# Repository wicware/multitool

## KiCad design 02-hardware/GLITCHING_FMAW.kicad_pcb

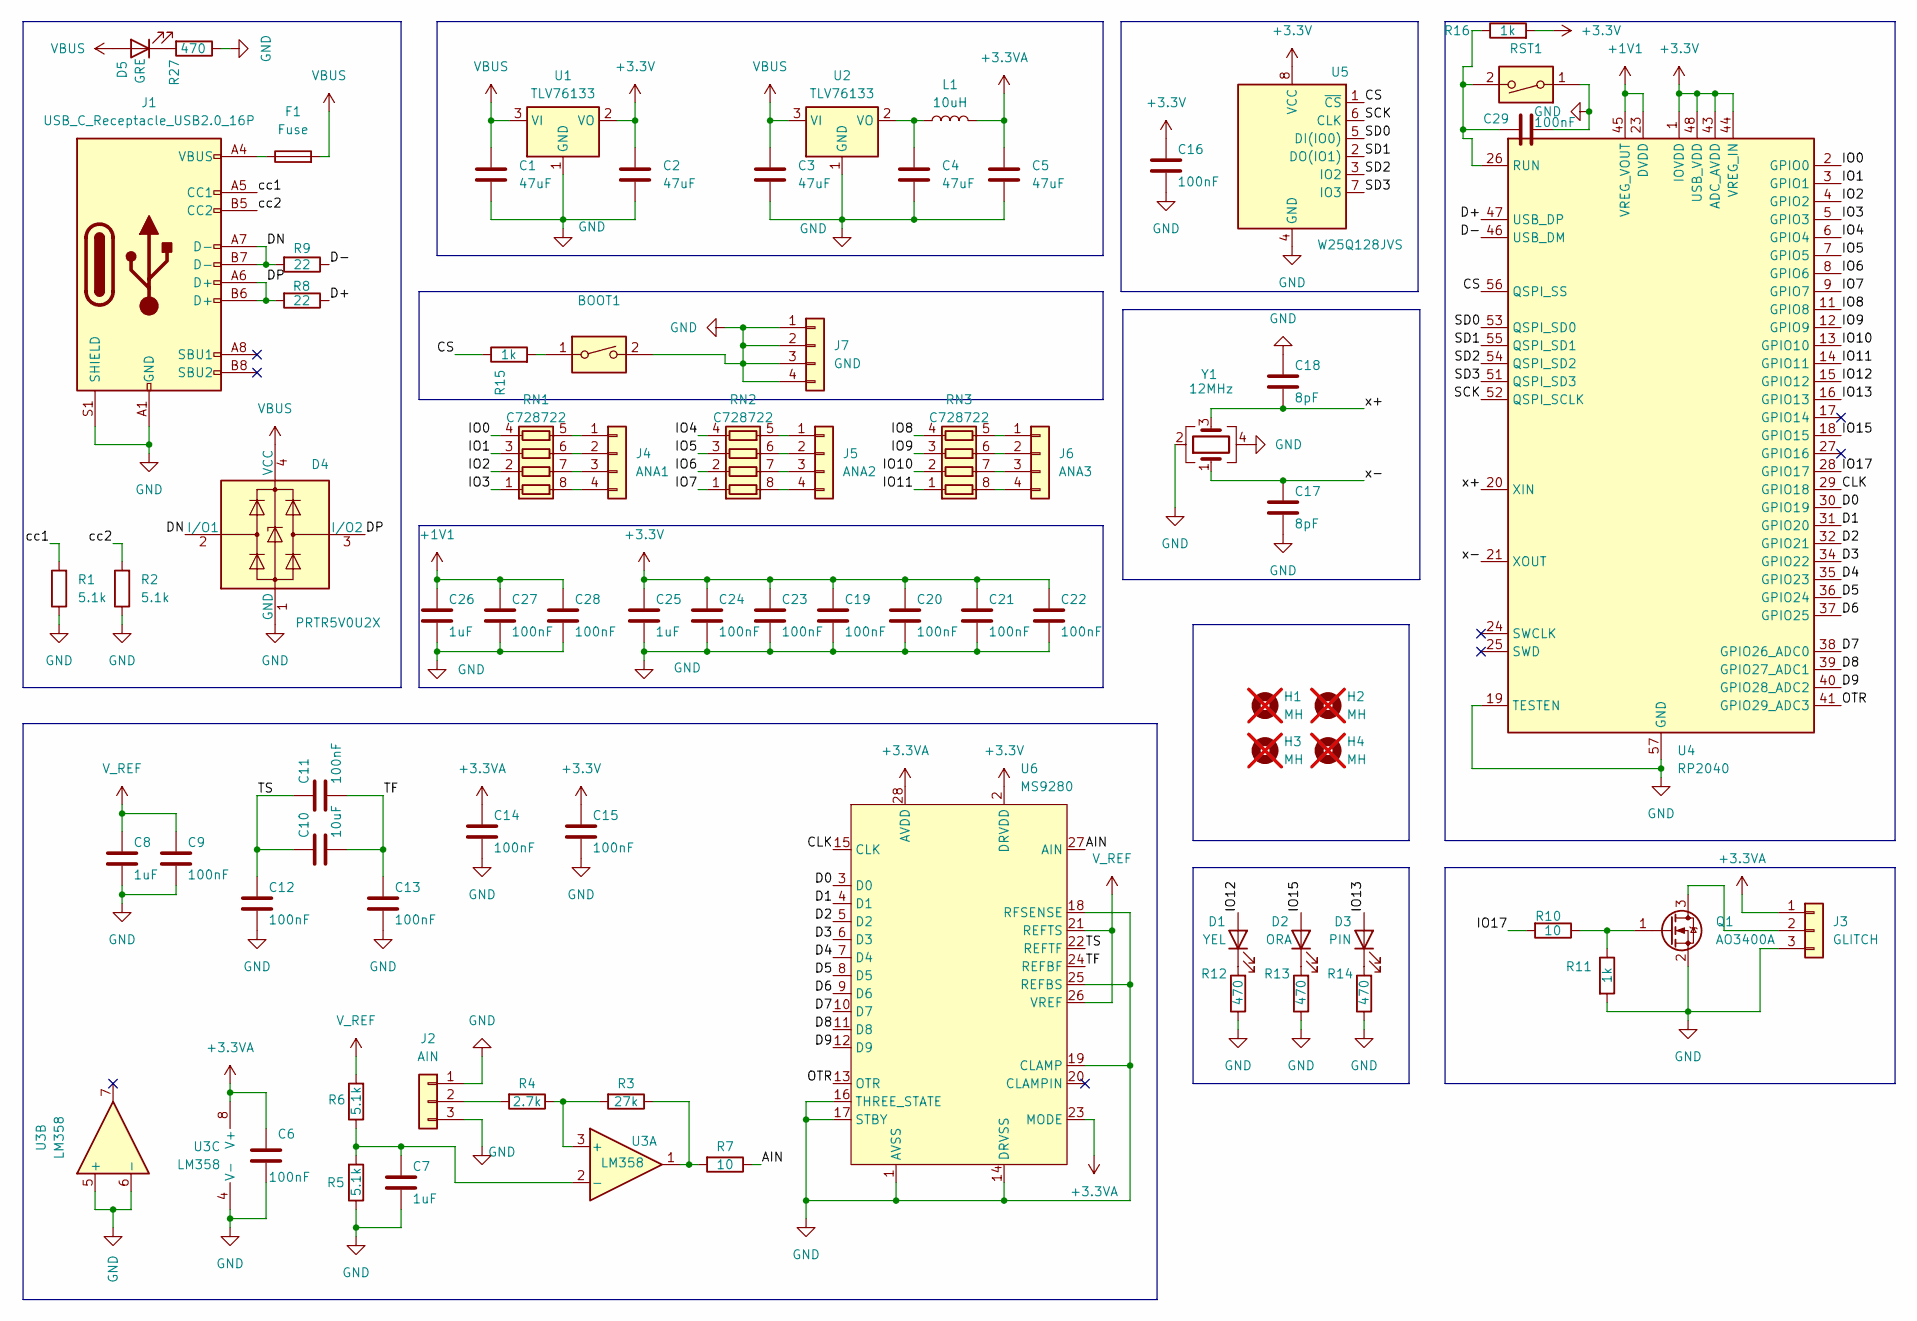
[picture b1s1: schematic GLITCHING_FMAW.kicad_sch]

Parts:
BOOT1: SW_DIP_x01; SW_SPST_CK_RS282G05A3
C1, C2, C3, C4, C5: 47uF; C_1206_3216Metric
C6, C9, C11, C12, C13, C14, C15, C16, C19, C20, C21, C22, C23, C24, C27, C28, C29: 100nF; C_0603_1608Metric
C7, C8, C25, C26: 1uF; C_0603_1608Metric
C10: 10uF; C_0603_1608Metric
C17, C18: 8pF; C_0603_1608Metric
D1: YEL; LED_0603_1608Metric
D2: ORA; LED_0603_1608Metric
D3: PIN; LED_0603_1608Metric
D4: PRTR5V0U2X; SOT-143; LCSC C5180302
D5: GRE; LED_0603_1608Metric
F1: Fuse; Fuse_1812_4532Metric; LCSC C142689
H1, H2, H3, H4: MH; MountingHole_2.2mm_M2_DIN965_Pad; not fitted
J1: USB_C_Receptacle_USB2.0_16P; USB_C_Receptacle_GCT_USB4105-xx-A_16P_TopMnt_Horizontal
J2: AIN; PinHeader_1x03_P2.54mm_Vertical
J3: GLITCH; PinHeader_1x03_P2.54mm_Vertical
J4: ANA1; PinHeader_1x04_P2.54mm_Vertical
J5: ANA2; PinHeader_1x04_P2.54mm_Vertical
J6: ANA3; PinHeader_1x04_P2.54mm_Vertical
J7: GND; PinHeader_1x04_P2.54mm_Vertical
L1: 10uH; L_Bourns_SRP7028A_7.3x6.6mm; LCSC C22463829
Q1: AO3400A; SOT-23; LCSC C20917
R1, R2, R5, R6: 5.1k; R_0603_1608Metric
R3: 27k; R_0603_1608Metric
R4: 2.7k; R_0603_1608Metric
R7, R10: 10; R_0603_1608Metric
R8, R9: 22; R_0603_1608Metric
R11, R15, R16: 1k; R_0603_1608Metric
R12, R13, R14, R27: 470; R_0603_1608Metric
RN1, RN2, RN3: C728722; R_Array_Concave_4x0402; LCSC C728722
RST1: SW_DIP_x01; SW_SPST_CK_RS282G05A3
U1, U2: TLV76133; SOT-223-3_TabPin2; LCSC C7527500
U3: LM358; SO-8_3.9x4.9mm_P1.27mm; LCSC C693063
U4: RP2040; QFN-56-1EP_7x7mm_P0.4mm_EP3.2x3.2mm
U5: W25Q128JVS; SOIC-8_5.23x5.23mm_P1.27mm; LCSC C97521
U6: MS9280; SSOP-28_5.3x10.2mm_P0.65mm; LCSC C1509021
Y1: 12MHz; Crystal_SMD_Abracon_ABM10-4Pin_2.5x2.0mm; LCSC C1985454

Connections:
+1V1: C26.1, C27.1, C28.1, U4.23 (DVDD), U4.45 (VREG_VOUT), U4.50 (DVDD)
+3.3V: C2.1, C15.1, C16.1, C19.1, C20.1, C21.1, C22.1, C23.1, C24.1, C25.1, R16.2, U1.2 (VO), U4.1 (IOVDD), U4.10 (IOVDD), U4.22 (IOVDD), U4.33 (IOVDD), U4.42 (IOVDD), U4.43 (ADC_AVDD), U4.44 (VREG_IN), U4.48 (USB_VDD), U4.49 (IOVDD), U5.8 (VCC), U6.2 (DRVDD)
+3.3VA: C5.1, C6.1, C14.1, J3.1, L1.2, U3.8 (V+), U6.23 (MODE), U6.28 (AVDD)
/AIN: R7.1, U6.27 (AIN)
/CLK: U4.29 (GPIO18), U6.15 (CLK)
/CS: R15.1, U4.56 (QSPI_SS), U5.1 (~CS)
/D0: U4.30 (GPIO19), U6.3 (D0)
/D1: U4.31 (GPIO20), U6.4 (D1)
/D2: U4.32 (GPIO21), U6.5 (D2)
/D3: U4.34 (GPIO22), U6.6 (D3)
/D4: U4.35 (GPIO23), U6.7 (D4)
/D5: U4.36 (GPIO24), U6.8 (D5)
/D6: U4.37 (GPIO25), U6.9 (D6)
/D7: U4.38 (GPIO26_ADC0), U6.10 (D7)
/D8: U4.39 (GPIO27_ADC1), U6.11 (D8)
/D9: U4.40 (GPIO28_ADC2), U6.12 (D9)
/D+: R8.1, U4.47 (USB_DP)
/D-: R9.1, U4.46 (USB_DM)
/DN: D4.2 (I/O1), J1.A7 (D-), J1.B7 (D-), R9.2
/DP: D4.3 (I/O2), J1.A6 (D+), J1.B6 (D+), R8.2
/IO0: RN1.4 (R4.1), U4.2 (GPIO0)
/IO1: RN1.3 (R3.1), U4.3 (GPIO1)
/IO2: RN1.2 (R2.1), U4.4 (GPIO2)
/IO3: RN1.1 (R1.1), U4.5 (GPIO3)
/IO4: RN2.4 (R4.1), U4.6 (GPIO4)
/IO5: RN2.3 (R3.1), U4.7 (GPIO5)
/IO6: RN2.2 (R2.1), U4.8 (GPIO6)
/IO7: RN2.1 (R1.1), U4.9 (GPIO7)
/IO8: RN3.4 (R4.1), U4.11 (GPIO8)
/IO9: RN3.3 (R3.1), U4.12 (GPIO9)
/IO10: RN3.2 (R2.1), U4.13 (GPIO10)
/IO11: RN3.1 (R1.1), U4.14 (GPIO11)
/IO12: D1.2 (A), U4.15 (GPIO12)
/IO13: D3.2 (A), U4.16 (GPIO13)
/IO15: D2.2 (A), U4.18 (GPIO15)
/IO17: R10.2, U4.28 (GPIO17)
/OTR: U4.41 (GPIO29_ADC3), U6.13 (OTR)
/SCK: U4.52 (QSPI_SCLK), U5.6 (CLK)
/SD0: U4.53 (QSPI_SD0), U5.5 (DI(IO0))
/SD1: U4.55 (QSPI_SD1), U5.2 (DO(IO1))
/SD2: U4.54 (QSPI_SD2), U5.3 (IO2)
/SD3: U4.51 (QSPI_SD3), U5.7 (IO3)
/TF: C10.2, C11.2, C13.1, U6.24 (REFBF)
/TS: C10.1, C11.1, C12.1, U6.22 (REFTF)
/cc1: J1.A5 (CC1), R1.2
/cc2: J1.B5 (CC2), R2.2
/x+: C18.2, U4.20 (XIN), Y1.3
/x-: C17.1, U4.21 (XOUT), Y1.1
GND: BOOT1.2, C1.2, C2.2, C3.2, C4.2, C5.2, C6.2, C7.2, C8.2, C9.2, C12.2, C13.2, C14.2, C15.2, C16.2, C17.2, C18.1, C19.2, C20.2, C21.2, C22.2, C23.2, C24.2, C25.2, C26.2, C27.2, C28.2, C29.2, D4.1 (GND), J1.A1 (GND), J1.A12 (GND), J1.B1 (GND), J1.B12 (GND), J1.S1 (SHIELD), J2.1, J2.3, J3.3, J7.1, J7.2, J7.3, J7.4, Q1.2 (S), R1.1, R2.1, R5.1, R11.2, R12.1, R13.1, R14.1, R27.1, RST1.1, U1.1 (GND), U2.1 (GND), U3.4 (V-), U3.5 (+), U3.6 (-), U4.19 (TESTEN), U4.57 (GND), U5.4 (GND), U6.1 (AVSS), U6.14 (DRVSS), U6.16 (THREE_STATE), U6.17 (STBY), U6.18 (RFSENSE), U6.19 (CLAMP), U6.25 (REFBS), Y1.2, Y1.4
unnamed: BOOT1.1, R15.2
unnamed: D1.1 (K), R12.2
unnamed: D2.1 (K), R13.2
unnamed: D3.1 (K), R14.2
unnamed: D5.1 (K), R27.2
unnamed: F1.1, J1.A4 (VBUS), J1.A9 (VBUS), J1.B4 (VBUS), J1.B9 (VBUS)
unnamed: J2.2, R4.2
unnamed: J3.2, Q1.3 (D)
unnamed: J4.1, RN1.5 (R4.2)
unnamed: J4.2, RN1.6 (R3.2)
unnamed: J4.3, RN1.7 (R2.2)
unnamed: J4.4, RN1.8 (R1.2)
unnamed: J5.1, RN2.5 (R4.2)
unnamed: J5.2, RN2.6 (R3.2)
unnamed: J5.3, RN2.7 (R2.2)
unnamed: J5.4, RN2.8 (R1.2)
unnamed: J6.1, RN3.5 (R4.2)
unnamed: J6.2, RN3.6 (R3.2)
unnamed: J6.3, RN3.7 (R2.2)
unnamed: J6.4, RN3.8 (R1.2)
unnamed: Q1.1 (G), R10.1, R11.1
unnamed: R3.1, R7.2, U3.1
unnamed: C4.1, L1.1, U2.2 (VO)
unnamed: R3.2, R4.1, U3.3 (+)
unnamed: C7.1, R5.2, R6.1, U3.2 (-)
unnamed: C29.1, R16.1, RST1.2, U4.26 (RUN)
VBUS: C1.1, C3.1, D4.4 (VCC), D5.2 (A), F1.2, U1.3 (VI), U2.3 (VI)
V_REF: C8.1, C9.1, R6.2, U6.21 (REFTS), U6.26 (VREF)

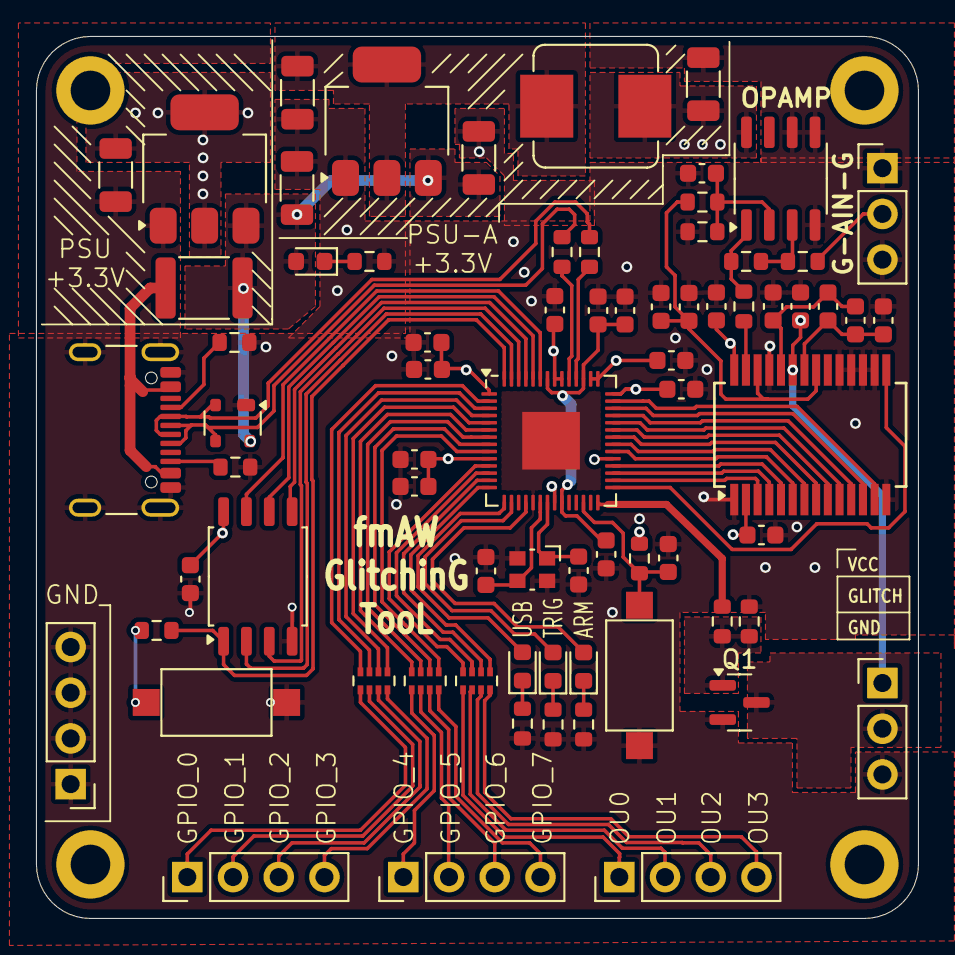
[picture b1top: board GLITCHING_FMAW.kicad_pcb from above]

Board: 4 copper layers, 49.0 x 49.0 mm, 77 parts (0 on the bottom side), 77 nets.

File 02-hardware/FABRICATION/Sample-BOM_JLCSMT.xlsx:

Comment | Designator | Footprint | JLCPCB Part #（optional）
47uF | C1 | Capacitor_SMD:C_1206_3216Metric
47uF | C2 | Capacitor_SMD:C_1206_3216Metric
47uF | C3 | Capacitor_SMD:C_1206_3216Metric
47uF | C4 | Capacitor_SMD:C_1206_3216Metric
47uF | C5 | Capacitor_SMD:C_1206_3216Metric
100nF | C6 | Capacitor_SMD:C_0603_1608Metric
1uF | C7 | Capacitor_SMD:C_0603_1608Metric
1uF | C8 | Capacitor_SMD:C_0603_1608Metric
100nF | C9 | Capacitor_SMD:C_0603_1608Metric
10uF | C10 | Capacitor_SMD:C_0603_1608Metric
100nF | C11 | Capacitor_SMD:C_0603_1608Metric
100nF | C12 | Capacitor_SMD:C_0603_1608Metric
100nF | C13 | Capacitor_SMD:C_0603_1608Metric
100nF | C14 | Capacitor_SMD:C_0603_1608Metric
100nF | C15 | Capacitor_SMD:C_0603_1608Metric
100nF | C16 | Capacitor_SMD:C_0603_1608Metric
8pF | C17 | Capacitor_SMD:C_0603_1608Metric
8pF | C18 | Capacitor_SMD:C_0603_1608Metric
100nF | C19 | Capacitor_SMD:C_0603_1608Metric
100nF | C20 | Capacitor_SMD:C_0603_1608Metric
100nF | C21 | Capacitor_SMD:C_0603_1608Metric
100nF | C22 | Capacitor_SMD:C_0603_1608Metric
100nF | C23 | Capacitor_SMD:C_0603_1608Metric
100nF | C24 | Capacitor_SMD:C_0603_1608Metric
1uF | C25 | Capacitor_SMD:C_0603_1608Metric
1uF | C26 | Capacitor_SMD:C_0603_1608Metric
100nF | C27 | Capacitor_SMD:C_0603_1608Metric
100nF | C28 | Capacitor_SMD:C_0603_1608Metric
YEL | D1 | LED_SMD:LED_0603_1608Metric
ORA | D2 | LED_SMD:LED_0603_1608Metric
PIN | D3 | LED_SMD:LED_0603_1608Metric
PRTR5V0U2X | D4 | Package_TO_SOT_SMD:SOT-143 | C5180302
GRE | D5 | LED_SMD:LED_0603_1608Metric
Fuse | F1 | Fuse:Fuse_1812_4532Metric | C142689
USB_C_Receptacle_USB2.0_16P | J1 | Connector_USB:USB_C_Receptacle_GCT_USB4105-xx-A_16P_TopMnt_Horizontal
AIN | J2 | Connector_PinHeader_2.54mm:PinHeader_1x03_P2.54mm_Vertical
GLITCH | J3 | Connector_PinHeader_2.54mm:PinHeader_1x03_P2.54mm_Vertical
ANA1 | J4 | Connector_PinHeader_2.54mm:PinHeader_1x04_P2.54mm_Vertical
ANA2 | J5 | Connector_PinHeader_2.54mm:PinHeader_1x04_P2.54mm_Vertical
ANA3 | J6 | Connector_PinHeader_2.54mm:PinHeader_1x04_P2.54mm_Vertical
GND | J7 | Connector_PinHeader_2.54mm:PinHeader_1x04_P2.54mm_Vertical
10uH | L1 | Inductor_SMD:L_Bourns_SRP7028A_7.3x6.6mm | C22463829
AO3400A | Q1 | Package_TO_SOT_SMD:SOT-223-3_TabPin2 | C20917
5.1k | R1 | Resistor_SMD:R_0603_1608Metric
5.1k | R2 | Resistor_SMD:R_0603_1608Metric
27k | R3 | Resistor_SMD:R_0603_1608Metric
2.7k | R4 | Resistor_SMD:R_0603_1608Metric
5.1k | R5 | Resistor_SMD:R_0603_1608Metric
5.1k | R6 | Resistor_SMD:R_0603_1608Metric
10 | R7 | Resistor_SMD:R_0603_1608Metric
22 | R8 | Resistor_SMD:R_0603_1608Metric
22 | R9 | Resistor_SMD:R_0603_1608Metric
10 | R10 | Resistor_SMD:R_0603_1608Metric
1k | R11 | Resistor_SMD:R_0603_1608Metric
470 | R12 | Resistor_SMD:R_0603_1608Metric
470 | R13 | Resistor_SMD:R_0603_1608Metric
470 | R14 | Resistor_SMD:R_0603_1608Metric
470 | R27 | Resistor_SMD:R_0603_1608Metric
C728722 | RN1 | Resistor_SMD:R_Array_Concave_4x0402 | C728722
C728722 | RN2 | Resistor_SMD:R_Array_Concave_4x0402 | C728722
C728722 | RN3 | Resistor_SMD:R_Array_Concave_4x0402 | C728722
TLV76133 | U1 | Package_TO_SOT_SMD:SOT-223-3_TabPin2 | C7527500
TLV76133 | U2 | Package_TO_SOT_SMD:SOT-223-3_TabPin2 | C7527500
LM358 | U3 | Package_SO:SO-8_3.9x4.9mm_P1.27mm | C693063
RP2040 | U4 | Package_DFN_QFN:QFN-56-1EP_7x7mm_P0.4mm_EP3.2x3.2mm
W25Q128JVS | U5 | Package_SO:SOIC-8_5.23x5.23mm_P1.27mm | C97521
MS9280 | U6 | Package_SO:SSOP-28_5.3x10.2mm_P0.65mm | C1509021
12MHz | Y1 | Crystal:Crystal_SMD_Abracon_ABM10-4Pin_2.5x2.0mm | C1985454

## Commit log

2025-12-10 update hw to mosfet | update expamples
2025-12-10 fix readme
2025-12-10 fix path
2025-12-10 fix name folder
2025-12-12 update readme info with clock glitch
